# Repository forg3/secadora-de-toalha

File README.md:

# Secador de Toalhas Inteligente em Alumínio (390 W / 127 V~)

Projeto completo de engenharia para um secador e aquecedor de toalhas de alto rendimento térmico, estruturado em perfis de alumínio e controlado por placa de circuito impresso dedicada (KiCad 10) baseada no microcontrolador ESP32-C3.

---

## 1. Objetivo do Projeto

Desenvolver um secador de toalhas residencial autônomo, seguro e com acabamento de produto comercial, capaz de secar e higienizar toalhas de banho de forma rápida, eficiente e com consumo racional de energia. O projeto une eletrônica de potência com isolamento galvânico estrito, firmware em C++17 com controle térmico por histerese, conectividade Wi-Fi para agendamentos e uma estrutura mecânica leve com elevada condutividade térmica.

---

## 2. O Problema Enfrentado

1. **Proliferação bacteriana e umidade crônica**: Toalhas úmidas em banheiros com baixa ventilação permanecem molhadas por longos períodos, propiciando proliferação de fungos, bactérias e odores desagradáveis.
2. **Ineficiência de modelos comerciais**: Secadores de toalha de entrada utilizam potências muito baixas (40 W a 70 W), funcionando apenas como aquecedores brandos e demorando horas para secar toalhas pesadas de algodão.
3. **Alto custo e robustez precária**: Modelos importados de maior potência utilizam estruturas pesadas em aço inox com resistências secas ou óleo térmico de difícil manutenção, com preços proibitivos no mercado nacional.
4. **Complexidade e risco elétrico**: O ambiente de banheiro (área molhada) exige rigorosa conformidade com normas de segurança (NBR 5410 / IEC 60950). Soluções improvisadas baseadas em relés mecânicos ou caixas industriais em trilho DIN resultam em cabeamento exposto, risco de choque elétrico e queima prematura por condensação de vapor.

---

## 3. Hipóteses e Soluções Avaliadas

Durante a concepção da engenharia do produto (documentada no comparativo técnico interativo `comparativo-secador-aluminio.html`), foram analisadas quatro grandes hipóteses de arquitetura:

### Hipótese A: Eletrônica Modular (Trilho DIN) vs. Placa de Circuito Impresso Dedicada
- **Módulos Industriais (Controlador + SSR + Fonte externa)**: Embora simplifique o circuito preliminar, a fiação necessária para interligar fonte chaveada, relé de estado sólido (SSR) e microcontrolador ocupa volume excessivo, encarece o conjunto (R$ 571 em eletrônica por unidade) e cria múltiplos pontos de falha mecânica por vibração ou corrosão de terminais.
- **Placa Dedicada Integrada (Solução Escolhida)**: A placa customizada de 115 × 75 mm reúne em uma única PCB de 2 camadas a fonte AC/DC isolada (HLK-PM01), o disparo do Triac via optoacoplador com zero-crossing (MOC3063) e o soquete do ESP32-C3 SuperMini. Elimina cabos soltos e reduz a montagem a conexões de bornes padronizados.

### Hipótese B: Elemento de Aquecimento: Cartuchos Blindados vs. Fio de Silicone
- **6 Cartuchos Resistivos de 500 mm**: Custo aproximado de R$ 420 sob encomenda, com rigidez mecânica que complica o roteamento interno nas dobras dos perfis e gera pontos de aquecimento concentrados.
- **Fio Aquecedor em Silicone (Solução Escolhida)**: Cabo flexível isolado com liga resistiva passando em ida e volta pelas 6 barras tubulares (~R$ 121). Proporciona aquecimento perfeitamente homogêneo ao longo de toda a extensão tubular, montagem simplificada e alta durabilidade sob dilatação térmica.

### Hipótese C: Material Estrutural: Aço Inoxidável vs. Perfis de Alumínio
- **Aço Inox**: Baixa condutividade térmica (~16 W/m·K), peso elevado e maior custo de usinagem e corte.
- **Alumínio Estrutural (Solução Escolhida)**: Excelente condutividade térmica (~205 W/m·K), garantindo transferência quase instantânea de calor do elemento interno para a superfície de contato da toalha. Além disso, o perfil externo de alumínio atua como dissipador térmico direto para o Triac de potência.

### Hipótese D: Estratégia de Controle Térmico e Conectividade
- **Termostato Bimetálico Simples (XH-W3001)**: Econômico, porém desprovido de temporização dinâmica, conectividade, curvas de histerese programáveis ou telemetria.
- **Microcontrolador ESP32-C3 (Solução Escolhida)**: Permite controle fino com histerese (50–60 °C ajustável), watchdog de segurança em tempo real, Modo Eco para economia de energia e interface Web Wi-Fi para acionamento programado (ex.: pré-aquecimento matinal e pós-banho).

---

## 4. Arquitetura de Hardware e Segurança em Camadas

O circuito opera em **127 V~ / 60 Hz**, demandando **3,1 A** em regime pleno (potência nominal de **390 W**):

```
[ Redes 127 V~ ] ──> Fusível T5A ──> Filtro MOV/X2 ──> Triac BTA16 ──> KSD301 (85°C) ──> Fusível Térmico (102°C) ──> Barras
                                                            ▲
                                        [ BARREIRA DE ISOLAÇÃO: 8 mm + Slot Fresado ]
                                                            │
[ Lado Baixa Tensão ] ──> HLK-PM01 (5V) ──> ESP32-C3 ──> MOC3063 (Zero-Cross) ──> NTC 10k + Display TM1637
```

### Domínio de Alta Tensão (HV - 127 V~)
- **Proteção Primária**: Fusível de ação retardada T5A contra curto-circuito, varistor de óxido metálico (MOV 14D431K) para supressão de surtos de rede e capacitor de segurança X2 de 100 nF / 275 VAC para filtragem de EMI.
- **Comutação de Potência**: Triac BTA16-600B montado externamente à PCB, parafusado diretamente no perfil de alumínio aterrado. A aba do encapsulamento TOP3/TO-220 isolada (RG) garante isolação elétrica total mantendo dissipação térmica passiva eficiente (~4 W de calor rejeitado).
- **Proteção Térmica Redundante em Hardware**:
  - Termostato bimetálico **KSD301 (85 °C NF)** em contato direto com a estrutura, interrompendo a linha de alimentação caso ocorra superaquecimento independente do microcontrolador.
  - Fusível térmico irreversível de **102 °C** em série como salvaguarda contra falha mecânica de contato do KSD301.

### Barreira de Isolação Física e Galvânica
- **Isolação Reforçada**: Distância de fuga (creepage) e isolação em ar (clearance) de **≥ 8 mm** entre trilhas de alta e baixa tensão, em conformidade com as normas IEC 60950 e IEC 60335.
- **Rasgo Fresado (Milling Slot)**: Ranhura de 2 × 55 mm na camada `Edge_Cuts` da placa sob a área de isolamento galvânico, impedindo arcos elétricos e correntes de fuga mesmo sob condensação de umidade.
- **Acoplamento Óptico**: Disparo através do optotriac **MOC3063TVM** com detector de passagem por zero (zero-crossing) e isolação galvânica de 5.000 V RMS.

### Domínio de Baixa Tensão (LV - 5 V / 3.3 V)
- **Alimentação**: Módulo AC/DC isolado **HLK-PM01** (tensão de isolamento de 3.000 V RMS).
- **Processamento**: Módulo ESP32-C3 SuperMini (Wi-Fi + BLE, RISC-V).
- **Sensoriamento**: Termistor NTC 10k B3950 inserido na barra principal para feedback térmico contínuo.
- **Interface Local**: Módulo de display TM1637 de 4 dígitos e botões táteis de ajuste.

---

## 5. Firmware e Lógica de Controle

O firmware foi desenvolvido em C++17 com separação completa entre regras de negócio (`firmware/src/control.h`) e drivers de hardware (`firmware/src/main.cpp`), permitindo compilação e testes unitários em ambiente Linux sem necessidade do emulador de hardware.

### Recursos de Software:
1. **Controle por Histerese**: Alvo ajustável (default 55 °C com histerese de 3 °C).
2. **Modo Eco**: Redução de 10 °C no setpoint e ciclo com modulação por tempo (máximo 5 minutos ligado a cada janela de 10 minutos).
3. **Classificação de Falhas de Sensor**:
   - Tensão ADC > 2.800 mV: Detecção de sensor aberto (fio solto).
   - Tensão ADC < 60 mV: Detecção de sensor em curto-circuito.
   - Temperatura lida < 0 °C ou > 75 °C: Interrupção imediata da condução do Triac.
   - Trava de proteção (lockout) após 3 leituras de falha consecutivas, exigindo reinicialização do dispositivo.
4. **Watchdog Timer**: Reinício automático do ESP32-C3 em caso de travamento do loop principal.

---

## 6. Estrutura do Repositório

```
├── comparativo-secador-aluminio.html      # Estudo técnico comparativo, custos e balanço térmico
├── Esquemático Completo do Secador...png  # Diagrama esquemático ilustrativo
├── Infográfico Técnico_ Secador...png     # Diagrama em blocos e fluxo de potência
├── pcb/                                   # Projeto de hardware no KiCad 10
│   ├── secador-toalha.kicad_pcb           # Layout da PCB (115 × 75 mm, 2 camadas)
│   ├── build_board.py                     # Script Python gerador da placa via pcbnew API
│   ├── fabricacao/                        # Pacote completo para fábrica (Turnkey PCBWay)
│   │   ├── secador-toalha-gerbers.zip     # Arquivos Gerber e furação
│   │   ├── secador-toalha-bom-pcbway.xlsx # Lista de componentes (BOM formatada)
│   │   ├── secador-toalha-posicao.csv     # Coordenadas Pick & Place (Centroid)
│   │   ├── secador-toalha-montagem.pdf    # Guia visual de montagem de componentes
│   │   └── pedido-pcbway.txt              # Instruções e parâmetros para cotação
│   └── gerbers/                           # Camadas gerber individuais (GTL, GBL, etc.)
└── firmware/                              # Firmware em C++17 para ESP32-C3
    ├── src/
    │   ├── control.h                      # Motor de regras e controle térmico puro
    │   └── main.cpp                       # Código principal (Arduino / PlatformIO)
    ├── test/
    │   └── test_control.cpp               # Suíte de testes unitários para execução em PC
    └── firmware.ino                       # Sketch Arduino compatível
```

---

## 7. Instruções de Fabricação e Montagem

1. **Placa de Circuito**: O pacote em `pcb/fabricacao/` contém todos os arquivos validados para cotação e montagem Turnkey (ex.: PCBWay). Todos os componentes da placa utilizam montagem Through-Hole (THT), facilitando inspeção e montagem manual.
2. **Gravação do Firmware**: Gravar o ESP32-C3 exclusivamente via porta USB-C com a placa desconectada da rede elétrica 127 V~.
3. **Comissionamento em Bancada**:
   - Utilize uma lâmpada incandescente de 60 W conectada em série no borne da carga (`J2`) durante o primeiro teste na tomada para validar o chaveamento zero-crossing sem risco de sobrecorrente.
   - Verifique com multímetro o aterramento do chassi e a atuação do termostato mecânico.
4. **Instalação Residencial (NBR 5410)**:
   - É mandatório ligar o pino de terra (PE) ao condutor de proteção da residência.
   - O circuito de tomada do banheiro deve ser protegido por Disjuntor Residual (DR) de alta sensibilidade (30 mA).

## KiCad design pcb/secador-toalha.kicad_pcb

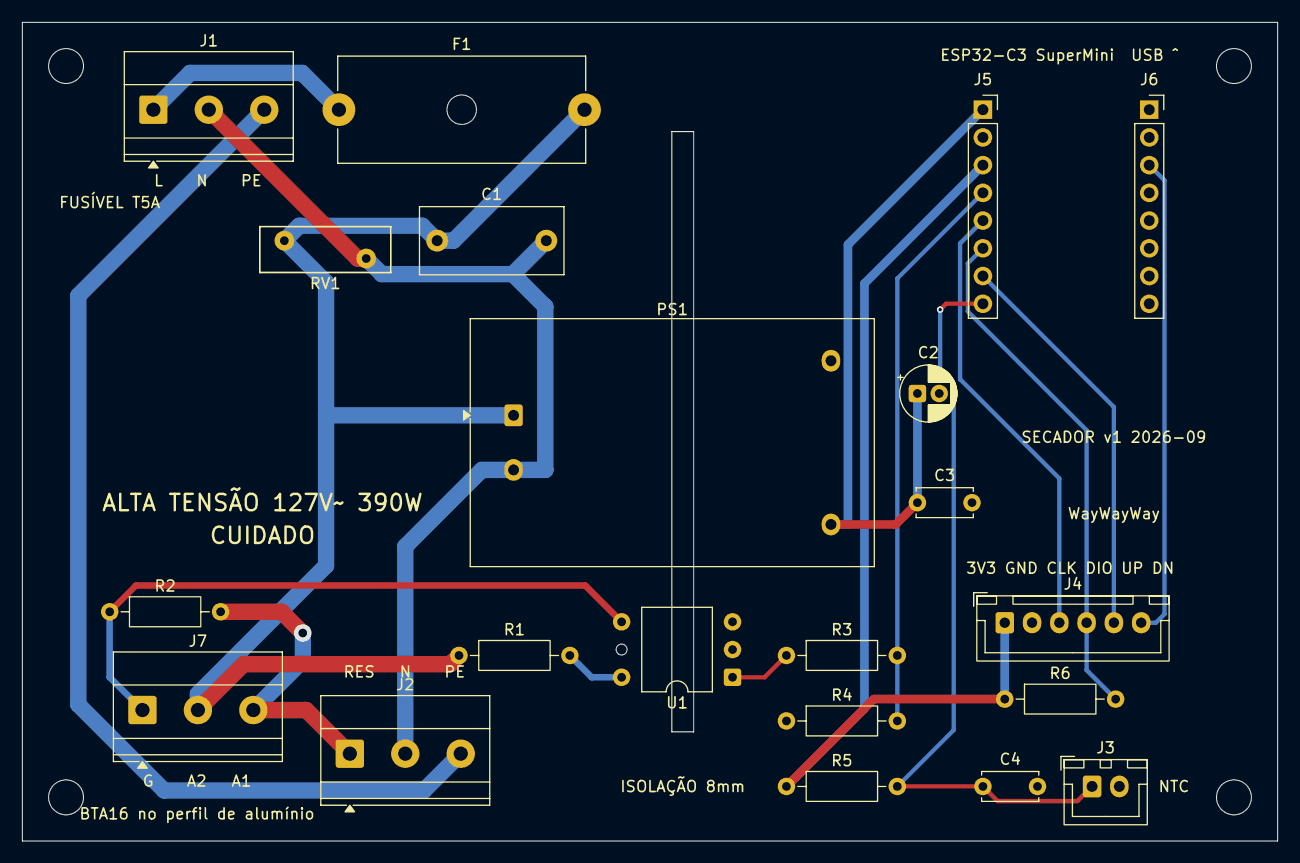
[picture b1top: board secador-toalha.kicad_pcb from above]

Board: 2 copper layers, 115.0 x 75.0 mm, 25 parts (0 on the bottom side), 17 nets.

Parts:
C1: 100nF X2 275V; C_Rect_L13.0mm_W6.0mm_P10.00mm_FKS3_FKP3_MKS4
C2: 10uF 16V; CP_Radial_D5.0mm_P2.00mm
C3, C4: 100nF; C_Disc_D5.0mm_W2.5mm_P5.00mm
F1: T5A 250V; Fuseholder_Cylinder-5x20mm_Schurter_0031_8201_Horizontal_Op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
H1, H2, H3, H4: MountingHole_3.2mm_M3
J1: AC_IN L/N/PE; TerminalBlock_Phoenix_MKDS-1,5-3-5.08_1x03_P5.08mm_Horizont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
J2: RES N PE; TerminalBlock_Phoenix_MKDS-1,5-3-5.08_1x03_P5.08mm_Horizont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
J3: NTC 10k; JST_XH_B2B-XH-A_1x02_P2.50mm_Vertical
J4: PAINEL; JST_XH_B6B-XH-A_1x06_P2.50mm_Vertical
J5: ESP32-C3 fila A; PinSocket_1x08_P2.54mm_Vertical
J6: ESP32-C3 fila B; PinSocket_1x08_P2.54mm_Vertical
J7: BTA16 G/A2/A1; TerminalBlock_Phoenix_MKDS-1,5-3-5.08_1x03_P5.08mm_Horizont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
PS1: HLK-PM01; Converter_ACDC_Hi-Link_HLK-PMxx
R1: 360R; R_Axial_DIN0207_L6.3mm_D2.5mm_P10.16mm_Horizontal
R2: 330R; R_Axial_DIN0207_L6.3mm_D2.5mm_P10.16mm_Horizontal
R3: 150R; R_Axial_DIN0207_L6.3mm_D2.5mm_P10.16mm_Horizontal
R4, R5, R6: 10k; R_Axial_DIN0207_L6.3mm_D2.5mm_P10.16mm_Horizontal
RV1: 14D431K; RV_Disc_D12mm_W4.2mm_P7.5mm
U1: MOC3063; DIP-6_W10.16mm

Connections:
+3V3: J4.1, J5.3, R5.1, R6.1
+5V: C2.1, C3.1, J5.1, PS1.4
AC_L: F1.1, J1.1
AC_L_FUSED: C1.1, F1.2, J7.2, PS1.1, R1.1, RV1.1
AC_N: C1.2, J1.2, J2.2, PS1.2, RV1.2
BTN_DN: J4.6, J6.3
BTN_UP: J4.5, J5.7
EARTH_PE: J1.3, J2.3
GND: C2.2, C3.2, C4.2, J3.2, J4.2, J5.2, PS1.3, R4.1, U1.2
HEAT_SW: J2.1, J7.3, R2.2
MOC_LED: R3.1, U1.1
MOC_OUT: R1.2, U1.6
NTC_ADC: C4.1, J3.1, J5.8, R5.2
TM_CLK: J4.3, J5.5
TM_DIO: J4.4, J5.6, R6.2
TRIAC_DRV: J5.4, R3.2, R4.2
TRIAC_GATE: J7.1, R2.1, U1.4

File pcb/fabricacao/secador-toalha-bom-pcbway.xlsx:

Item # | Designator | Qty | Manufacturer | Mfg Part # | Description / Value | Package/Footprint | Type | Your Instructions / Notes
1 | PS1 | 1 | Hi-Link | HLK-PM01 | AC-DC module 100-240VAC to 5VDC 3W isolated | HLK-PMxx THT | THT
2 | U1 | 1 | onsemi | MOC3063TVM | Zero-cross triac optocoupler 600V | DIP-6 0.4in (10.16mm) wide lead | THT | Must be wide-lead (T option). Pin 5 goes into the unplated hole - do not solder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
3 | F1 | 1 | Schurter | 0031.8201 | Fuse holder 5x20mm PCB open | 5x20 horizontal P22.5mm | THT
4 | F1 (fuse) | 1 | Littelfuse | 0218005.HXP | Fuse 5x20mm 5A 250VAC slow-blow | 5x20mm | THT | Insert into F1 holder
5 | RV1 | 1 | TDK | B72214S0271K101 | Varistor S14K275 (14D431K equivalent) | Disc 14mm P7.5mm | THT | Equivalent 14D431K accepted
6 | C1 | 1 | Any | - | Capacitor 100nF 275VAC class X2 | Box P10mm W<=6mm L<=13mm | THT | Safety-rated X2 only
7 | C2 | 1 | Any | - | Aluminium electrolytic 10uF 16V | Radial D5mm P2mm | THT | Observe polarity
8 | C3,C4 | 2 | Any | - | Ceramic 100nF 50V | Disc P5mm | THT
9 | R1 | 1 | Any | - | Resistor 360R 1/4W 1% metal film | Axial DIN0207 P10.16mm | THT
10 | R2 | 1 | Any | - | Resistor 330R 1/4W 1% metal film | Axial DIN0207 P10.16mm | THT
11 | R3 | 1 | Any | - | Resistor 150R 1/4W 1% metal film | Axial DIN0207 P10.16mm | THT
12 | R4,R5,R6 | 3 | Any | - | Resistor 10k 1/4W 1% metal film | Axial DIN0207 P10.16mm | THT
13 | J1,J2,J7 | 3 | Phoenix Contact | 1715734 | Terminal block 3 pos 5.08mm MKDS 1.5/3-5.08 | THT P5.08mm | THT | Wire entry facing board edge as in silkscreen
14 | J3 | 1 | JST | B2B-XH-A(LF)(SN) | Header XH 2 pos 2.5mm vertical | JST XH | THT
15 | J4 | 1 | JST | B6B-XH-A(LF)(SN) | Header XH 6 pos 2.5mm vertical | JST XH | THT
16 | J5,J6 | 2 | Any | - | Female pin header 1x8 2.54mm vertical | 1x08 P2.54mm | THT | Sockets only - ESP32 module is NOT placed
17 | Q1 (off-board) | 1 | STMicroelectronics | BTA16-600BRG | Triac 16A 600V insulated tab | TO-220AB | DNP | Do not place. Ship loose with the boards
18 | J3/J4 mating | 1 | JST | XHP-2 + XHP-6 + SXH-001T-P0.6 x8 | Housings and crimp contacts | - | DNP | Ship loose
